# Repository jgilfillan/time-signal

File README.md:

# time-signal

A radio time-signal transmitter for the Raspberry Pi. It sends **JJY**, **MSF**,
**WWVB** or **DCF77** so radio-controlled watches and clocks set themselves,
wherever you live.

This fork adds a hardware design (a Pi Zero pHAT, ferrite antenna and
3D-printed case), a web control panel, and scripts to turn a Pi into a
plug-and-play gift for fellow watch enthusiasts.

| pHAT | Enclosure |
|---|---|
|  |  |

## Where to start

| I want to… | Go to |
|---|---|
| Understand the circuit | [hardware/schematic](hardware/schematic/README.md) |
| Try it on a breadboard | [hardware/breadboard](hardware/breadboard/README.md) |
| Wind and tune the antenna | [hardware/antenna](hardware/antenna/README.md) |
| Order the assembled PCB | [hardware/pcb](hardware/pcb/README.md) |
| Print the case | [hardware/enclosure](hardware/enclosure/README.md) |
| Run it on my own Pi | [Software](#software) below |
| Make units to give away | [pi-setup](pi-setup/README.md) |
| I've been given one | [docs/QUICKSTART.md](docs/QUICKSTART.md) |

## How it works

The Pi generates the carrier (40, 60 or 77.5 kHz) on GPIO4 (pin 7) with its
hardware clock, and switches it on and off each second to encode the time
the way the real station does. A MOSFET drives a ferrite antenna tuned to
the carrier frequency. Range is a few metres, which is plenty for watches on
a shelf nearby. See [hardware](hardware/README.md) for the details.

**Supported Pis:** upstream tested the transmitter on the Pi Zero W, Pi 3
Model B and Pi 4 Model B. The Pi Zero 2 W uses the same chip family as the
Pi 3 and is expected to work. The pHAT and enclosure fit the Zero W and
Zero 2 W; get the **WH** versions (header pre-soldered) or solder a 40-pin
header on yourself.

## Software

### Install

On Raspberry Pi OS:

```bash
git clone https://github.com/jgilfillan/time-signal.git
cd time-signal
sudo ./install.sh
```

The installer:

1. compiles the `time-signal` binary
2. creates a Python virtual environment in `web/.venv` and installs Flask
3. optionally helps you set a static IP address (skipped with `--non-interactive`)
4. installs and starts the `time-signal-web` service on port **8080**

Then open `http://<pi-hostname-or-ip>:8080`.

### Web interface

From any phone or computer on your network you can:

- start and stop transmission, and choose the station
- see the time being sent, whether the clock is synced, and a live log
- turn on **autostart**, so it transmits whenever the Pi boots

**It won't transmit until the Pi's clock has synced with internet time.** A
Pi has no battery-backed clock, so before that it can be hours or days out and
would set your watches wrong. Autostart waits (the page shows *Waiting for
time sync*), and the Start button explains why it can't start yet.

**Each station sends its own country's time** (Japan for JJY, Germany for
DCF77, UK for MSF, UTC with US daylight-saving bits for WWVB), whatever time
zone the Pi is set to.

Settings are saved to `web/config.json`. The service can be tuned with
environment variables in its systemd unit:

| Variable | Default | Purpose |
|---|---|---|
| `TIMESIGNAL_PORT` | `8080` | Web server port |
| `TIMESIGNAL_CONFIG` | `web/config.json` | Where settings are saved |
| `TIMESIGNAL_DEFAULT_SERVICE` | `DCF77` | Station used before any setting is saved |
| `TIMESIGNAL_DEFAULT_AUTOSTART` | `0` | Autostart before any setting is saved |
| `TIMESIGNAL_REQUIRE_TIME_SYNC` | `1` | Refuse to transmit until the clock is synced |

Managing the service:

```bash
sudo systemctl status time-signal-web      # is it running?
sudo journalctl -u time-signal-web -f      # live logs
sudo systemctl restart time-signal-web     # after changing settings
sudo systemctl disable --now time-signal-web   # stop and don't start at boot
```

To uninstall, disable the service as above, then
`sudo rm /etc/systemd/system/time-signal-web.service && sudo systemctl daemon-reload`.

### Command line

```bash
sudo ./time-signal -s JJY60      # transmit the time signal
sudo ./time-signal -s JJY60 -c   # carrier only, for tuning the antenna
```

| Option | Meaning |
|---|---|
| `-s <service>` | `DCF77`, `WWVB`, `JJY40`, `JJY60` or `MSF` |
| `-c` | Carrier only, no time code (for tuning) |
| `-v` | Verbose: show the modulation envelope |
| `-h` | Help |

Run directly, the binary uses the Pi's time zone. For JJY that means running
it with `TZ=Asia/Tokyo` unless the Pi is set to Japan time; the web
interface does this for you.

Build only the binary with `make`. It needs `gcc` and must run as root.

### Requirements

- Raspberry Pi OS (Bookworm or later recommended), with `gcc` and `make`
- Python 3.9 or newer for the web interface

### Tests

```bash
python3 -m unittest discover -s tests -v
```

They stub out the transmitter and `timedatectl`, so they run on any machine
with Flask installed.

## Repository layout

```
time-signal.c, time-services.c, clock-control.c   transmitter (C)
web/                 Flask control panel
install.sh           installs the binary and web service
tests/               web server tests
hardware/            circuit, breadboard, antenna, PCB, enclosure
pi-setup/            scripts for plug-and-play give-away units
docs/QUICKSTART.md   guide for people receiving a unit
```

## Legal

These are very low-power transmitters, but rules on radio transmission vary.
Check yours before using one (in Australia, the ACMA LIPD class licence).

## Credits and references

The transmitter is by Pierre Brial ([harlock974/time-signal](https://github.com/harlock974/time-signal)),
based on Henner Zeller's [txtempus](https://github.com/hzeller/txtempus).
Compared with txtempus, time-signal is written in C, builds without CMake, and
needs no attenuation pin, so the hardware is simpler.

1. Slevin, Cohen and Golkowski (2021), "Wideband VLF/LF Transmission from an
   Electrically-Small Antenna by Means of Time-Varying Non-Reciprocity via
   High-Speed Switches", URSI GASS 2021.
2. Ferrite antennas: <https://www.electronics-notes.com/articles/antennas-propagation/ferrite-rod-bar-antenna/basics-tutorial.php>
3. Designing longer-range transmitters (txtempus discussion): <https://github.com/hzeller/txtempus/issues/8>
4. Andreas Spiess, designing a DCF77 transmitter: <https://youtu.be/6SHGAEhnsYk>
5. Wikipedia: [DCF77](https://en.wikipedia.org/wiki/DCF77),
   [WWVB](https://en.wikipedia.org/wiki/WWVB),
   [MSF](https://en.wikipedia.org/wiki/Time_from_NPL_(MSF)),
   [JJY](https://en.wikipedia.org/wiki/JJY).

Licensed under the GNU GPL v3 (see [LICENSE](LICENSE)).

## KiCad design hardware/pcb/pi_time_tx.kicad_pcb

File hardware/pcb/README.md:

# pHAT PCB (v1.2)

A 65 × 30 mm board that plugs straight onto a Raspberry Pi Zero WH / Zero 2 WH
(a Zero W or Zero 2 W with the 40-pin header fitted; a plain Zero W / Zero 2 W
needs a 2 × 20 male header soldered on first).
JLCPCB makes and fully assembles it, including both connectors. You only
screw the antenna leads into the terminal.

| Top | Bottom |
|---|---|
|  |  |

- Circuit: see [../schematic](../schematic/README.md). Parallel LC tank,
  AO3400A MOSFET, C3/C4/C5 empty for tuning.
- **Wi-Fi keep-out:** the strip along the bottom edge (over the Pi's built-in
  Wi-Fi antenna, between the mini-HDMI and USB sockets) has no copper on
  either layer, so the board doesn't block Wi-Fi or Bluetooth. Its placement
  for the Zero 2 W is inferred from the Zero W's antenna position.
- Design rule check passes with every connection made.

## Files

| File | What it is |
|---|---|
| `pi_time_tx.kicad_pro/.kicad_sch/.kicad_pcb` | KiCad 7 project |
| `pi_time_tx_gerbers_JLCPCB.zip` | Gerbers + drill files to upload |
| `jlcpcb_bom.csv` | Parts list with LCSC numbers (9 lines) |
| `jlcpcb_cpl.csv` | Placement file (9 parts) |
| `scripts/` | Python scripts that generated the board (see below) |

## Ordering 5 boards at JLCPCB

1. jlcpcb.com → **Order now** → upload `pi_time_tx_gerbers_JLCPCB.zip`.
   2 layers, 65 × 30 mm, qty 5, 1.6 mm, lead-free HASL, any colour.
2. Tick **PCB Assembly**, PCBA qty 5.
   - Choose **Standard** assembly (Economic can't do through-hole parts or
     both sides).
   - Assembly side: **both sides**. J1 goes on the bottom, everything else
     on the top.
3. Upload `jlcpcb_bom.csv` and `jlcpcb_cpl.csv`.
   - C3, C4 and C5 are intentionally left empty.
   - Both connectors are factory-fitted: J1 (40-pin socket, C2977589) and
     J2 (screw terminal, C8465).
4. In the placement preview, check and rotate anything that's wrong:
   - Q1 (SOT-23): pin-1 dot top-left, single pin (drain) on the right.
   - C1, C2, C6, R1, R2, R3 centred on their pads.
   - J1 on the bottom, centred over its 40 holes.
   - J2's wire openings facing the right-hand board edge.

Check prices and stock on the quote screen; four parts carry JLC's
extended-part fee.

| Ref | Part | LCSC |
|---|---|---|
| Q1 | AO3400A, SOT-23 | C20917 |
| R1 | 220 Ω 1206 | C17957 |
| R2 | 470 Ω 0603 | C23179 |
| R3 | 100 kΩ 0603 | C25803 |
| C1 | 10 nF C0G 50 V 1206 | C64713 |
| C2 | 1.5 nF C0G 50 V 1206 | C105972 |
| C6 | 10 µF 25 V 0805 | C15850 |
| J1 | 2 × 20 female header, 8.5 mm | C2977589 |
| J2 | 2-pin screw terminal, 5.08 mm | C8465 |

## After the boards arrive

- Wind the [antenna](../antenna/README.md) and screw its two leads into J2
  (either way round).
- Mount on the Pi with M2.5 × 11 mm male-female standoffs (8.5 mm socket plus
  the Pi header's 2.5 mm plastic). Step-by-step instructions are in the
  [enclosure guide](../enclosure/README.md#fitting-the-phat-to-the-pi), which
  is designed for this stack.
- If a board needs trimming, add a 1206 C0G capacitor at C3/C4 or a leaded
  one at C5, and tune as in the [antenna guide](../antenna/README.md#tuning).

## Editing or regenerating

The KiCad files can be edited directly in KiCad 7 or later. They were
generated by the scripts in `scripts/`, which need KiCad's Python module
(`pcbnew`):

```bash
cd hardware/pcb
python3 scripts/gen_sch.py pi_time_tx.kicad_sch
kicad-cli sch export netlist -o /tmp/net.net pi_time_tx.kicad_sch
python3 scripts/gen_pcb.py pi_time_tx.kicad_pcb /tmp/net.net
python3 scripts/fill_drc.py pi_time_tx.kicad_pcb /tmp/drc.rpt   # fills zones, runs DRC
```

Before exporting Gerbers and the placement file, set the drill/place origin
to the board's bottom-left corner (100, 130 mm). If you edit the board by
hand in KiCad, don't re-run the generators, because they'd overwrite your
changes.

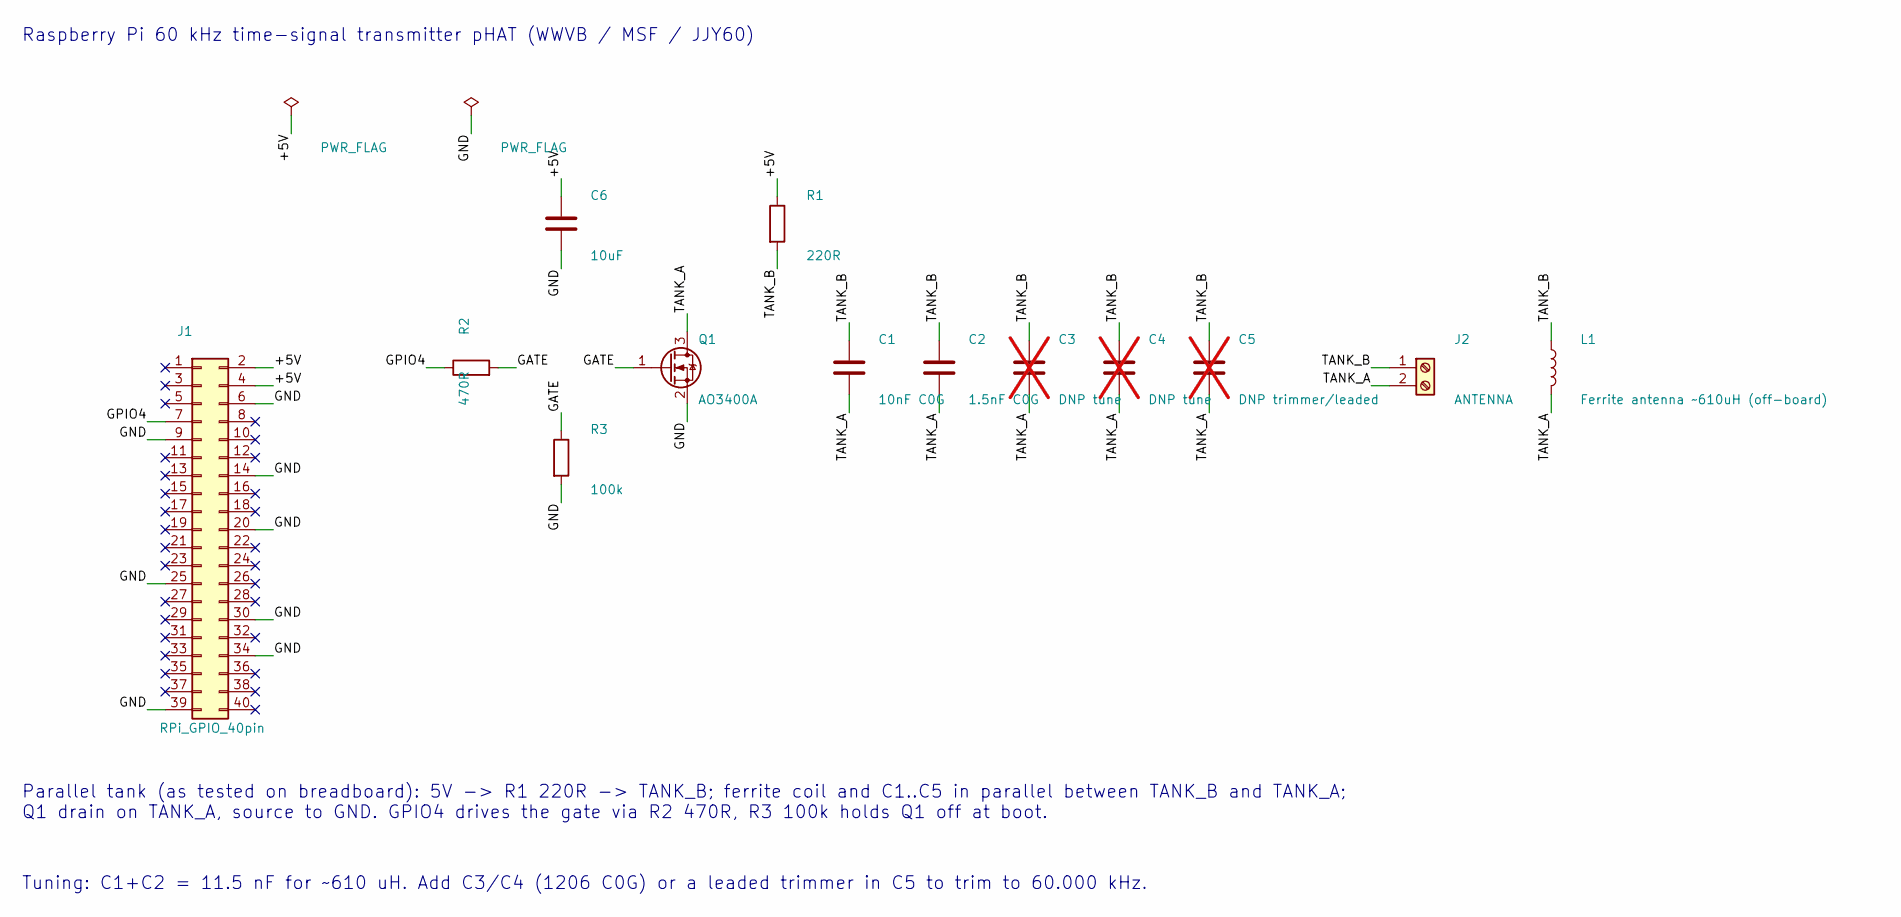
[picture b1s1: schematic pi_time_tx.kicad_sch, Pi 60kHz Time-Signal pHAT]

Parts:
C1: 10nF C0G; C_1206_3216Metric; LCSC C64713
C2: 1.5nF C0G; C_1206_3216Metric; LCSC C105972
C3, C4: DNP tune; C_1206_3216Metric; not fitted
C5: DNP trimmer/leaded; C_Disc_D5.0mm_W2.5mm_P5.00mm; not fitted
C6: 10uF; C_0805_2012Metric; LCSC C15850
J1: RPi_GPIO_40pin; PinSocket_2x20_P2.54mm_Vertical; LCSC C2977589
J2: ANTENNA; TerminalBlock_Phoenix_MKDS-1,5-2-5.08_1x02_P5.08mm_Horizont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; LCSC C8465
L1: Ferrite antenna ~610uH (off-board)
Q1: AO3400A; SOT-23; LCSC C20917
R1: 220R; R_1206_3216Metric; LCSC C17957
R2: 470R; R_0603_1608Metric; LCSC C23179
R3: 100k; R_0603_1608Metric; LCSC C25803

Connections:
+5V: C6.1, J1.2, J1.4, R1.1
GATE: Q1.1 (G), R2.2, R3.1
GND: C6.2, J1.6, J1.9, J1.14, J1.20, J1.25, J1.30, J1.34, J1.39, Q1.2 (S), R3.2
GPIO4: J1.7, R2.1
TANK_A: C1.2, C2.2, C3.2, C4.2, C5.2, J2.2, L1.2, Q1.3 (D)
TANK_B: C1.1, C2.1, C3.1, C4.1, C5.1, J2.1, L1.1, R1.2

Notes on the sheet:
Raspberry Pi 60 kHz time-signal transmitter pHAT (WWVB / MSF / JJY60)
Parallel tank (as tested on breadboard): 5V -> R1 220R -> TANK_B; ferrite coil and C1..C5 in parallel between TANK_B and TANK_A; Q1 drain on TANK_A, source to GND. GPIO4 drives the gate via R2 470R, R3 100k holds Q1 off at boot.
Tuning: C1+C2 = 11.5 nF for ~610 uH. Add C3/C4 (1206 C0G) or a leaded trimmer in C5 to trim to 60.000 kHz.

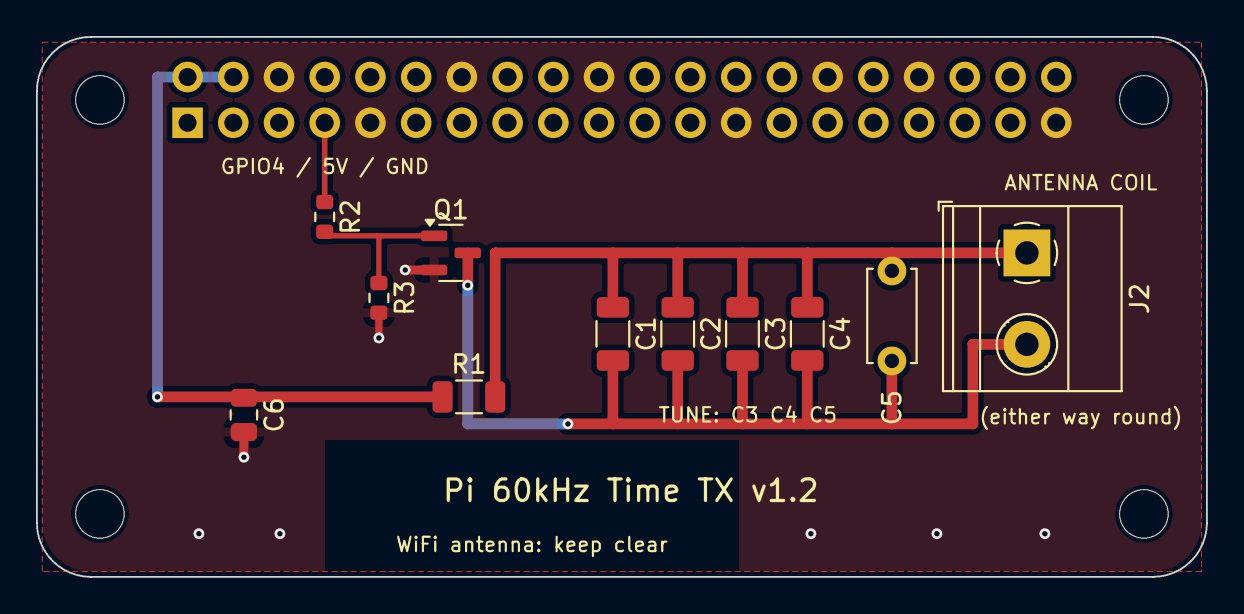
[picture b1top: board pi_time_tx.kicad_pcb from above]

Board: 2 copper layers, 65.0 x 30.0 mm, 16 parts (1 on the bottom side), 6 nets.

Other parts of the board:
H1, H2, H3, H4: M2.5; MountingHole_2.7mm_M2.5

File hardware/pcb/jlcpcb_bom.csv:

Comment,Designator,Footprint,LCSC Part #
AO3400A,Q1,SOT-23,C20917
220R 1206 0.25W,R1,1206,C17957
470R,R2,0603,C23179
100k,R3,0603,C25803
10nF C0G 50V,C1,1206,C64713
1.5nF C0G 50V,C2,1206,C105972
10uF 25V,C6,0805,C15850
2x20 female header 2.54mm 8.5mm,J1,2x20 P2.54 THT,C2977589
Screw terminal 2P 5.08mm,J2,1x2 P5.08 THT,C8465

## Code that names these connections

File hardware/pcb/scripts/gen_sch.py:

"""Generate the KiCad 7 schematic for the Pi 60 kHz time-signal pHAT.
Symbols are copied from the installed KiCad libraries; every pin gets a short
wire stub and a net label so connectivity is exact and checkable with ERC."""
import re, uuid, math, sys

LIB = "/usr/share/kicad/symbols/"
OUT = sys.argv[1]

def u(): return str(uuid.uuid4())

# ---------- tiny s-expression helpers ----------
def extract_block(text, start):
    depth = 0
    for i in range(start, len(text)):
        c = text[i]
        if c == '"':
            # skip string
            j = i + 1
            while text[j] != '"':
                j += 2 if text[j] == '\\' else 1
            continue
        if c == '(':
            depth += 1
        elif c == ')':
            depth -= 1
            if depth == 0:
                return text[start:i + 1]
    raise ValueError

def get_symbol(lib, name):
    txt = open(LIB + lib + ".kicad_sym").read()
    i = txt.find('(symbol "%s"' % name)
    blk = extract_block(txt, i)
    # rename top-level to lib:name (sub-units keep plain names)
    blk = blk.replace('(symbol "%s"' % name, '(symbol "%s:%s"' % (lib, name), 1)
    pins = {}
    for m in re.finditer(r'\(pin \w+ \w+\s*\(at ([-\d.]+) ([-\d.]+) ([-\d.]+)\).*?\(number "([^"]+)"', blk, re.S):
        x, y, a, num = m.groups()
        pins[num] = (float(x), float(y), float(a))
    return blk, pins

SYMS = {}
def need(lib, name):
    key = lib + ":" + name
    if key not in SYMS:
        SYMS[key] = get_symbol(lib, name)
    return key

parts = []      # symbol instances
wires = []
labels = []
noconn = []
texts = []

def rot(px, py, r):
    # symbol coords (y up) -> sheet offset (y down), rotated by r deg CCW
    x, y = px, -py
    t = math.radians(r)
    return (round(x * math.cos(t) + y * math.sin(t), 4),
            round(-x * math.sin(t) + y * math.cos(t), 4))

def place(lib, name, ref, value, x, y, r=0, fp="", props=None, nets=None,
          in_bom=True, on_board=True, dnp=False, stub=2.54, lbl=None):
    key = need(lib, name)
    blk, pins = SYMS[key]
    parts.append(dict(key=key, ref=ref, value=value, x=x, y=y, r=r, fp=fp,
                      props=props or {}, pins=list(pins.keys()),
                      in_bom=in_bom, on_board=on_board, dnp=dnp,
                      lbl=lbl or (4, -4, 4, 4.5)))
    for num, (px, py, pa) in pins.items():
        ox, oy = rot(px, py, r)
        ex, ey = x + ox, y + oy
        net = (nets or {}).get(num)
        if net is None:
            noconn.append((ex, ey))
            continue
        # outward direction = pin angle + 180, rotated
        ang = math.radians(pa + 180 + r)
        dx, dy = round(math.cos(ang) * stub, 4), round(-math.sin(ang) * stub, 4)
        wx, wy = round(ex + dx, 4), round(ey + dy, 4)
        wires.append(((ex, ey), (wx, wy)))
        # label rotation so text reads away from pin
        deg = (pa + 180 + r) % 360
        labels.append((net, wx, wy, {0: 0, 90: 90, 180: 180, 270: 270}.get(round(deg) % 360, 0)))

# ---------------- the circuit ----------------
# J1: Raspberry Pi 40-pin header (female socket on the pHAT)
GND_PINS = ["6", "9", "14", "20", "25", "30", "34", "39"]
j1nets = {"2": "+5V", "4": "+5V", "7": "GPIO4"}
for p in GND_PINS: j1nets[p] = "GND"
place("Connector_Generic", "Conn_02x20_Odd_Even", "J1", "RPi_GPIO_40pin", 50.8, 88.9,
      fp="Connector_PinSocket_2.54mm:PinSocket_2x20_P2.54mm_Vertical", props={"LCSC": "C2977589"}, nets=j1nets,
      lbl=(-3.5, -28, -6, 28))

# Gate drive
place("Device", "R", "R2", "470R", 88.9, 66.04, r=90, lbl=(-1, -4.5, -1, 5.5), fp="Resistor_SMD:R_0603_1608Metric",
      props={"LCSC": "C23179"}, nets={"1": "GPIO4", "2": "GATE"})
place("Device", "R", "R3", "100k", 101.6, 78.74, r=0, fp="Resistor_SMD:R_0603_1608Metric",
      props={"LCSC": "C25803"}, nets={"1": "GATE", "2": "GND"})
place("Transistor_FET", "BSS138", "Q1", "AO3400A", 116.84, 66.04, r=0,
      fp="Package_TO_SOT_SMD:SOT-23", props={"LCSC": "C20917"},
      nets={"1": "GATE", "2": "GND", "3": "TANK_A"})
# Pull-up / current limit
place("Device", "R", "R1", "220R", 132.08, 45.72, r=0, fp="Resistor_SMD:R_1206_3216Metric",
      props={"LCSC": "C17957"}, nets={"1": "+5V", "2": "TANK_B"})
# Series tuning capacitors (all in parallel with each other)
caps = [("C1", "10nF C0G", "C64713", False, "Capacitor_SMD:C_1206_3216Metric"),
        ("C2", "1.5nF C0G", "C105972", False, "Capacitor_SMD:C_1206_3216Metric"),
        ("C3", "DNP tune", "", True, "Capacitor_SMD:C_1206_3216Metric"),
        ("C4", "DNP tune", "", True, "Capacitor_SMD:C_1206_3216Metric"),
        ("C5", "DNP trimmer/leaded", "", True, "Capacitor_THT:C_Disc_D5.0mm_W2.5mm_P5.00mm")]
for i, (ref, val, lc, dnp, fp) in enumerate(caps):
    place("Device", "C", ref, val, 142.24 + i * 12.7, 66.04, r=0, fp=fp,
          props={"LCSC": lc} if lc else {}, nets={"1": "TANK_B", "2": "TANK_A"},
          in_bom=not dnp, dnp=dnp)
# Antenna terminal and the off-board ferrite coil
place("Connector", "Screw_Terminal_01x02", "J2", "ANTENNA", 223.52, 66.04, r=0,
      fp="TerminalBlock_Phoenix:TerminalBlock_Phoenix_MKDS-1,5-2-5.08_1x02_P5.08mm_Horizontal",
      props={"LCSC": "C8465"}, nets={"1": "TANK_B", "2": "TANK_A"})
place("Device", "L", "L1", "Ferrite antenna ~610uH (off-board)", 241.3, 66.04, r=0,
      nets={"1": "TANK_B", "2": "TANK_A"}, in_bom=False, on_board=False)
# Supply decoupling
place("Device", "C", "C6", "10uF", 101.6, 45.72, r=0, fp="Capacitor_SMD:C_0805_2012Metric",
      props={"LCSC": "C15850"}, nets={"1": "+5V", "2": "GND"})
# Power flags
place("power", "PWR_FLAG", "#FLG01", "PWR_FLAG", 63.5, 30.48, nets={"1": "+5V"})
place("power", "PWR_FLAG", "#FLG02", "PWR_FLAG", 88.9, 30.48, nets={"1": "GND"})

texts.append(("Raspberry Pi 60 kHz time-signal transmitter pHAT (WWVB / MSF / JJY60)", 25.4, 20.32))
texts.append(("Parallel tank (as tested on breadboard): 5V -> R1 220R -> TANK_B; ferrite coil and C1..C5 in parallel between TANK_B and TANK_A;\\nQ1 drain on TANK_A, source to GND. GPIO4 drives the gate via R2 470R, R3 100k holds Q1 off at boot.", 25.4, 130.0))
texts.append(("Tuning: C1+C2 = 11.5 nF for ~610 uH. Add C3/C4 (1206 C0G) or a leaded trimmer in C5 to trim to 60.000 kHz.", 25.4, 140.0))

# ---------------- write file ----------------
o = []
o.append('(kicad_sch (version 20230121) (generator eeschema)\n  (uuid %s)\n  (paper "A4")' % u())
o.append('  (title_block (title "Pi 60kHz Time-Signal pHAT") (rev "1.2") (date "2026-11-17"))')
o.append('  (lib_symbols')
for k, (blk, _) in SYMS.items():
    o.append(blk)
o.append('  )')
for (a, b) in wires:
    o.append('  (wire (pts (xy %s %s) (xy %s %s)) (stroke (width 0) (type default)) (uuid %s))' % (a[0], a[1], b[0], b[1], u()))
for (net, x, y, r) in labels:
    just = "left" if r in (0, 90) else "right"
    o.append('  (label "%s" (at %s %s %d) (fields_autoplaced) (effects (font (size 1.27 1.27)) (justify %s bottom)) (uuid %s))' % (net, x, y, r, just, u()))
for (x, y) in noconn:
    o.append('  (no_connect (at %s %s) (uuid %s))' % (x, y, u()))
for (t, x, y) in texts:
    o.append('  (text "%s" (at %s %s 0) (effects (font (size 1.8 1.8)) (justify left bottom)) (uuid %s))' % (t, x, y, u()))
root = u()
for p in parts:
    pin_s = "\n".join('    (pin "%s" (uuid %s))' % (n, u()) for n in p["pins"])
    prop_lines = []
    pidx = 4
    for k, v in p["props"].items():
        prop_lines.append('    (property "%s" "%s" (at %s %s 0) (effects (font (size 1.27 1.27)) hide))' % (k, v, p["x"], p["y"]))
    hide_ref = " hide" if p["ref"].startswith("#") else ""
    o.append('''  (symbol (lib_id "%s") (at %s %s %d) (unit 1)
    (in_bom %s) (on_board %s) (dnp %s) (fields_autoplaced)
    (uuid %s)
    (property "Reference" "%s" (at %s %s 0) (effects (font (size 1.27 1.27)) (justify left)%s))
    (property "Value" "%s" (at %s %s 0) (effects (font (size 1.27 1.27)) (justify left)))
    (property "Footprint" "%s" (at %s %s 0) (effects (font (size 1.27 1.27)) hide))
    (property "Datasheet" "~" (at %s %s 0) (effects (font (size 1.27 1.27)) hide))
%s
%s
    (instances (project "pi_time_tx" (path "/%s" (reference "%s") (unit 1))))
  )''' % (p["key"], p["x"], p["y"], p["r"],
         "yes" if p["in_bom"] else "no", "yes" if p["on_board"] else "no", "yes" if p["dnp"] else "no",
         u(), p["ref"], p["x"] + p["lbl"][0], p["y"] + p["lbl"][1], hide_ref, p["value"], p["x"] + p["lbl"][2], p["y"] + p["lbl"][3],
         p["fp"], p["x"], p["y"], p["x"], p["y"], "\n".join(prop_lines), pin_s, root, p["ref"]))
o.append('  (sheet_instances (path "/" (page "1")))\n)')
txt = "\n".join(o).replace("(uuid %s)\n  (paper" % "", "(paper")
# set root uuid consistently
txt = re.sub(r'\(kicad_sch \(version 20230121\) \(generator eeschema\)\n  \(uuid [^)]+\)',
             '(kicad_sch (version 20230121) (generator eeschema)\n  (uuid %s)' % root, txt, count=1)
open(OUT, "w").write(txt)
print("pins found:", {k: len(v[1]) for k, v in SYMS.items()})

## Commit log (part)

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2026-05-23 feat: add web UI and web server for controlling time-signal
2026-05-23 fix: log OSError internally instead of exposing it to the client
2026-05-24 feat: enhance web UI to load configuration and sync active service during transmission
